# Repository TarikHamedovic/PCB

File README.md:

# Printed Circuit Board Projects

This github repo contains my PCB projects.

## Printed Circuit Board(PCB) Workshop

The workshop was held at the Faculty of Electrical Engineering in Sarajevo, participants were guided through the comprehensive process of manually crafting a Printed Circuit Board (PCB), from the initial design phase in software to the physical realization involving drilling and soldering. The centerpiece of this hands-on session was the construction of a simple yet effective audio amplifier circuit, centered around the versatile LM386 Integrated Circuit (IC). The design phase is done in Proteus because most students at the faculty are familiar with the software.

For educational purposes, we opted to design the PCB as a single-layer board with through-hole components. While it's feasible to construct a more compact version, we intentionally enlarged the board's dimensions. This decision was made to accommodate a safer and more participant-friendly drilling experience. Ensuring ease of handling and reducing the risk of errors during the manual drilling process were our primary considerations, making the workshop accessible and engaging for attendees, regardless of their prior experience with PCB fabrication.

Schematic of Audio Amplifier Circuit             |  PCB Layout of Audio Amplifier Circuit
:-------------------------:|:-------------------------:
  |  

## Ultrasonic Speaker

The PCB developed was a component of my Bachelor's Thesis, which focused on creating an ultrasonic directional speaker. To achieve this, I employed a digital modulation method utilizing an STM32 Nucleo microcontroller. Specifically, I designed a custom shield equipped with all necessary components to interface with the Nucleo board. Additionally, I designed an ultrasonic phased array to facilitate the directional output of ultrasonic waves. The PCB was made in Eagle software.

Schematic of STM32 Shield             |  PCB Layout of STM32 Shield
:-------------------------:|:-------------------------:
  |  

Schematic of Transducer Array             |  PCB Layout of Transducer Array
:-------------------------:|:-------------------------:
  |

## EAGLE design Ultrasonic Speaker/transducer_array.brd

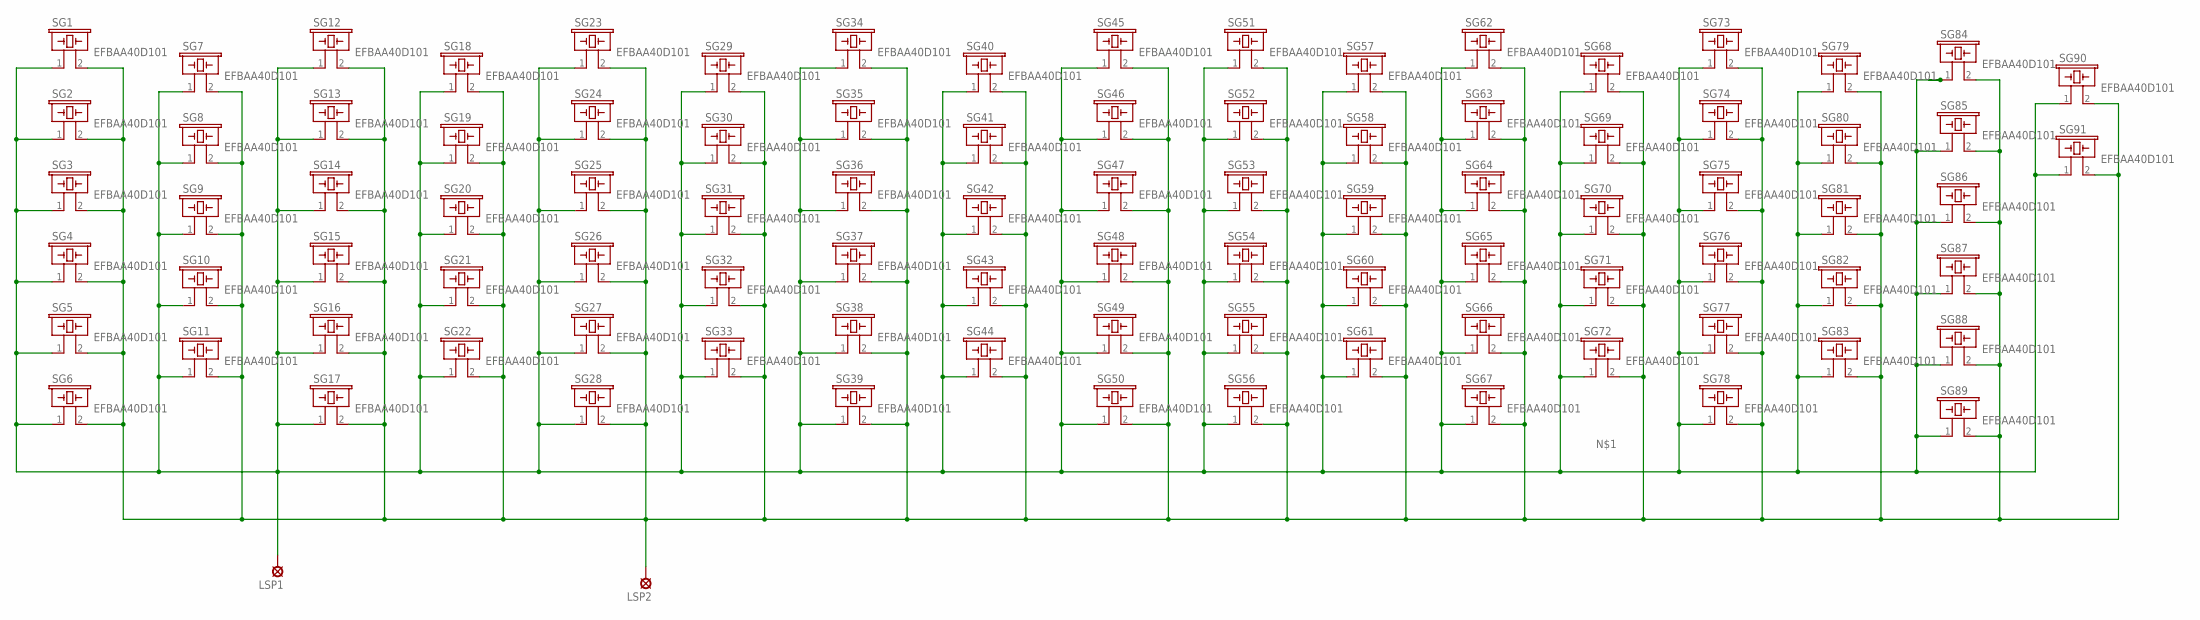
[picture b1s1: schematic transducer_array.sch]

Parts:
LSP1, LSP2: LSP10
SG1, SG2, SG3, SG4, SG5, SG6, SG7, SG8, SG9, SG10, SG11, SG12, SG13, SG14, SG15, SG16, SG17, SG18, SG19, SG20, SG21, SG22, SG23, SG24, SG25, SG26, SG27, SG28, SG29, SG30, SG31, SG32, SG33, SG34, SG35, SG36, SG37, SG38, SG39, SG40, SG41, SG42, SG43, SG44, SG45, SG46, SG47, SG48, SG49, SG50, SG51, SG52, SG53, SG54, SG55, SG56, SG57, SG58, SG59, SG60, SG61, SG62, SG63, SG64, SG65, SG66, SG67, SG68, SG69, SG70, SG71, SG72, SG73, SG74, SG75, SG76, SG77, SG78, SG79, SG80, SG81, SG82, SG83, SG84, SG85, SG86, SG87, SG88, SG89, SG90, SG91: EFBAA40D101

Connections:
unnamed: LSP1.MP, SG1.1, SG2.1, SG3.1, SG4.1, SG5.1, SG6.1, SG7.1, SG8.1, SG9.1, SG10.1, SG11.1, SG12.1, SG13.1, SG14.1, SG15.1, SG16.1, SG17.1, SG18.1, SG19.1, SG20.1, SG21.1, SG22.1, SG23.1, SG24.1, SG25.1, SG26.1, SG27.1, SG28.1, SG29.1, SG30.1, SG31.1, SG32.1, SG33.1, SG34.1, SG35.1, SG36.1, SG37.1, SG38.1, SG39.1, SG40.1, SG41.1, SG42.1, SG43.1, SG44.1, SG45.1, SG46.1, SG47.1, SG48.1, SG49.1, SG50.1, SG51.1, SG52.1, SG53.1, SG54.1, SG55.1, SG56.1, SG57.1, SG58.1, SG59.1, SG60.1, SG61.1, SG62.1, SG63.1, SG64.1, SG65.1, SG66.1, SG67.1, SG68.1, SG69.1, SG70.1, SG71.1, SG72.1, SG73.1, SG74.1, SG75.1, SG76.1, SG77.1, SG78.1, SG79.1, SG80.1, SG81.1, SG82.1, SG83.1, SG84.1, SG85.1, SG86.1, SG87.1, SG88.1, SG89.1, SG90.1, SG91.1
unnamed: LSP2.MP, SG1.2, SG2.2, SG3.2, SG4.2, SG5.2, SG6.2, SG7.2, SG8.2, SG9.2, SG10.2, SG11.2, SG12.2, SG13.2, SG14.2, SG15.2, SG16.2, SG17.2, SG18.2, SG19.2, SG20.2, SG21.2, SG22.2, SG23.2, SG24.2, SG25.2, SG26.2, SG27.2, SG28.2, SG29.2, SG30.2, SG31.2, SG32.2, SG33.2, SG34.2, SG35.2, SG36.2, SG37.2, SG38.2, SG39.2, SG40.2, SG41.2, SG42.2, SG43.2, SG44.2, SG45.2, SG46.2, SG47.2, SG48.2, SG49.2, SG50.2, SG51.2, SG52.2, SG53.2, SG54.2, SG55.2, SG56.2, SG57.2, SG58.2, SG59.2, SG60.2, SG61.2, SG62.2, SG63.2, SG64.2, SG65.2, SG66.2, SG67.2, SG68.2, SG69.2, SG70.2, SG71.2, SG72.2, SG73.2, SG74.2, SG75.2, SG76.2, SG77.2, SG78.2, SG79.2, SG80.2, SG81.2, SG82.2, SG83.2, SG84.2, SG85.2, SG86.2, SG87.2, SG88.2, SG89.2, SG90.2, SG91.2

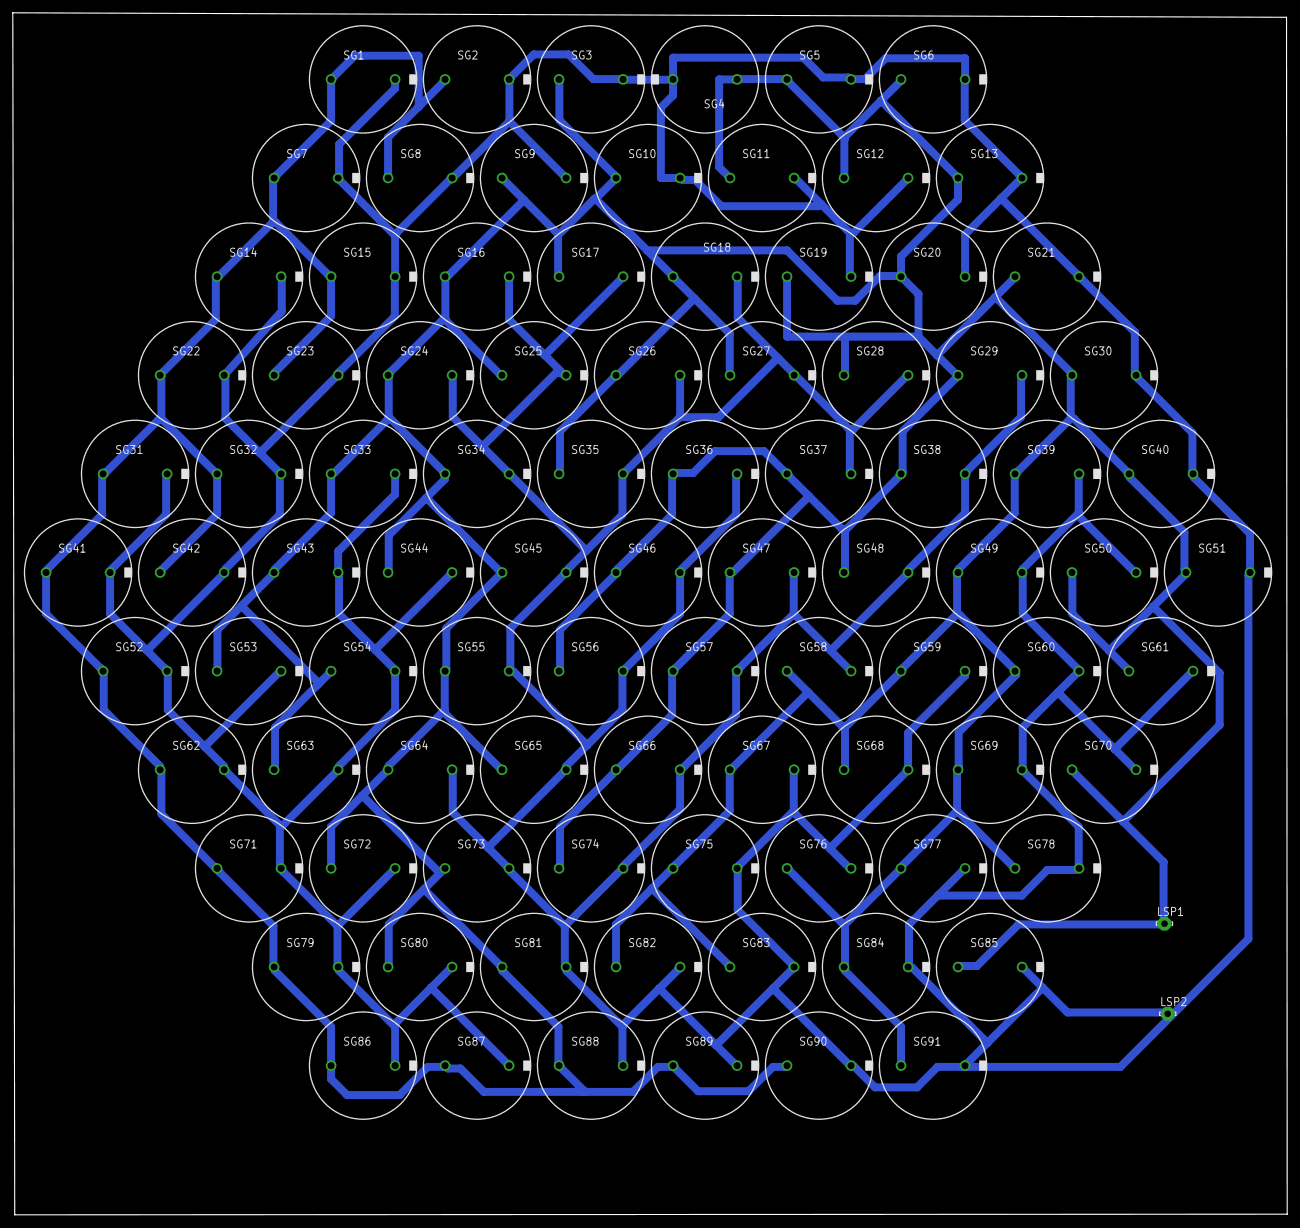
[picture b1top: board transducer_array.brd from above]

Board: 2 copper layers, 199.0 x 187.7 mm, 93 parts (0 on the bottom side), 2 nets.

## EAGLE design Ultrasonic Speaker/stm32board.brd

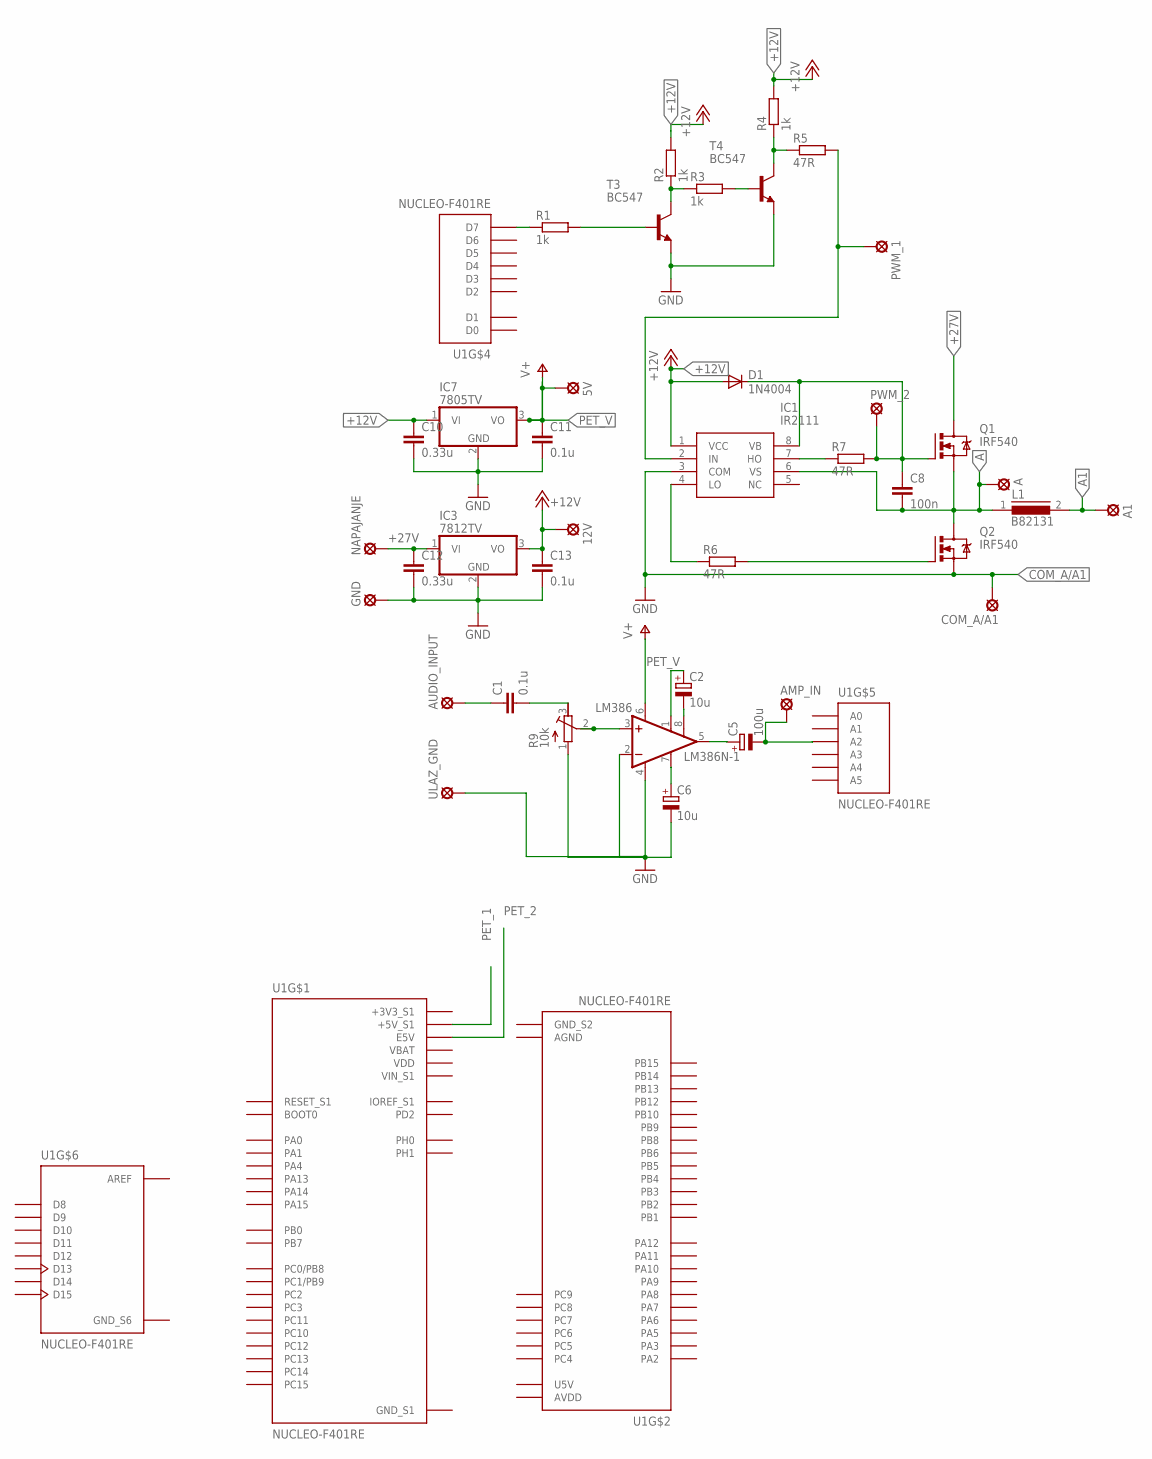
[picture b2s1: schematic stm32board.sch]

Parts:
5V, 12V: LSP10
A, A1: LSP10
AMP_IN: LSP10
AUDIO_INPUT: LSP10
C1, C11, C13: 0.1u; C050-030X075
C2, C6: 10u; E2,5-6E
C5: 100u; E2,5-6E
C8: 100n; C050-030X075
C10, C12: 0.33u; C050-030X075
COM_A/A1: LSP10
D1: 1N4004; DO41-10
GND: LSP10
IC1: IR2111; DIP762W56P254L988H533Q8N
IC3: 7812TV; TO220V
IC7: 7805TV; TO220V
L1: B82131; SUKW1-17
LM386: LM386N-1; DIL08
NAPAJANJE: LSP10
PWM_1, PWM_2: LSP10
Q1, Q2: IRF540; TO220BV
R1, R2, R3, R4: 1k; 0207/12
R5, R6, R7: 47R; 0207/12
R9: 10k; RTRIM3339P
T3, T4: BC547; TO92
U1: NUCLEO-F401RE; ST_NUCLEO-F401RE
ULAZ_GND: LSP10

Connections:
+3V3: U1.CN6_4 (+3V3)
+3V3_S1: U1.CN7_16 (+3V3_S1)
+12V: 12V.MP, C10.1, C13.1, D1.A, IC1.1 (VCC), IC3.3 (VO), IC7.1 (VI), R2.2, R4.2
+27V: C12.1, IC3.1 (VI), NAPAJANJE.MP, Q1.D
A: A.MP, C8.2, IC1.6 (VS), L1.1, Q1.S, Q2.D
A1: A1.MP, L1.2
AGND: U1.CN10_32 (AGND)
AREF: U1.CN5_8 (AREF)
AUDIO_INPUT: AUDIO_INPUT.MP, C1.1
AVDD: U1.CN10_7 (AVDD)
COM_A/A1: COM_A/A1.MP, IC1.3 (COM), Q2.S
GND: C6.-, C10.2, C11.2, C12.2, C13.2, GND.MP, IC3.2 (GND), IC7.2 (GND), LM386.2 (-IN), LM386.4 (GND), R9.1 (A), T3.1 (E), T4.1 (E), U1.CN6_6 (GND), U1.CN6_7 (GND), ULAZ_GND.MP
GND_S1: U1.CN7_8 (GND_S1), U1.CN7_19 (GND_S1), U1.CN7_20 (GND_S1), U1.CN7_22 (GND_S1)
GND_S2: U1.CN10_9 (GND_S2), U1.CN10_20 (GND_S2)
GND_S6: U1.CN5_7 (GND_S6)
unnamed: C5.+, LM386.5 (OUT)
unnamed: AMP_IN.MP, C5.-, U1.CN8_3 (A2)
unnamed: C2.-, LM386.8 (GAIN)
unnamed: C6.+, LM386.7 (BYPASS)
unnamed: R1.1, U1.CN9_8 (D7)
unnamed: C1.2, R9.3 (E)
unnamed: C2.+, LM386.1 (GAIN)
unnamed: LM386.3 (+IN), R9.2 (S)
unnamed: R1.2, T3.2 (B)
unnamed: R2.1, R3.1, T3.3 (C)
unnamed: R4.1, R5.1, T4.3 (C)
unnamed: R3.2, T4.2 (B)
unnamed: IC1.7 (HO), R7.1
unnamed: C8.1, D1.C, IC1.8 (VB), PWM_2.MP, Q1.G, R7.2
unnamed: IC1.4 (LO), R6.1
unnamed: Q2.G, R6.2
unnamed: IC1.2 (IN), PWM_1.MP, R5.2
PET_1: U1.CN7_18 (+5V_S1)
PET_2: U1.CN7_6 (E5V)
PET_V: 5V.MP, C11.1, IC7.3 (VO), LM386.6 (VS), U1.CN6_5 (+5V)
U5V: U1.CN10_8 (U5V)
VBAT: U1.CN7_33 (VBAT)
VDD: U1.CN7_5 (VDD)
VIN: U1.CN6_8 (VIN)
VIN_S1: U1.CN7_24 (VIN_S1)

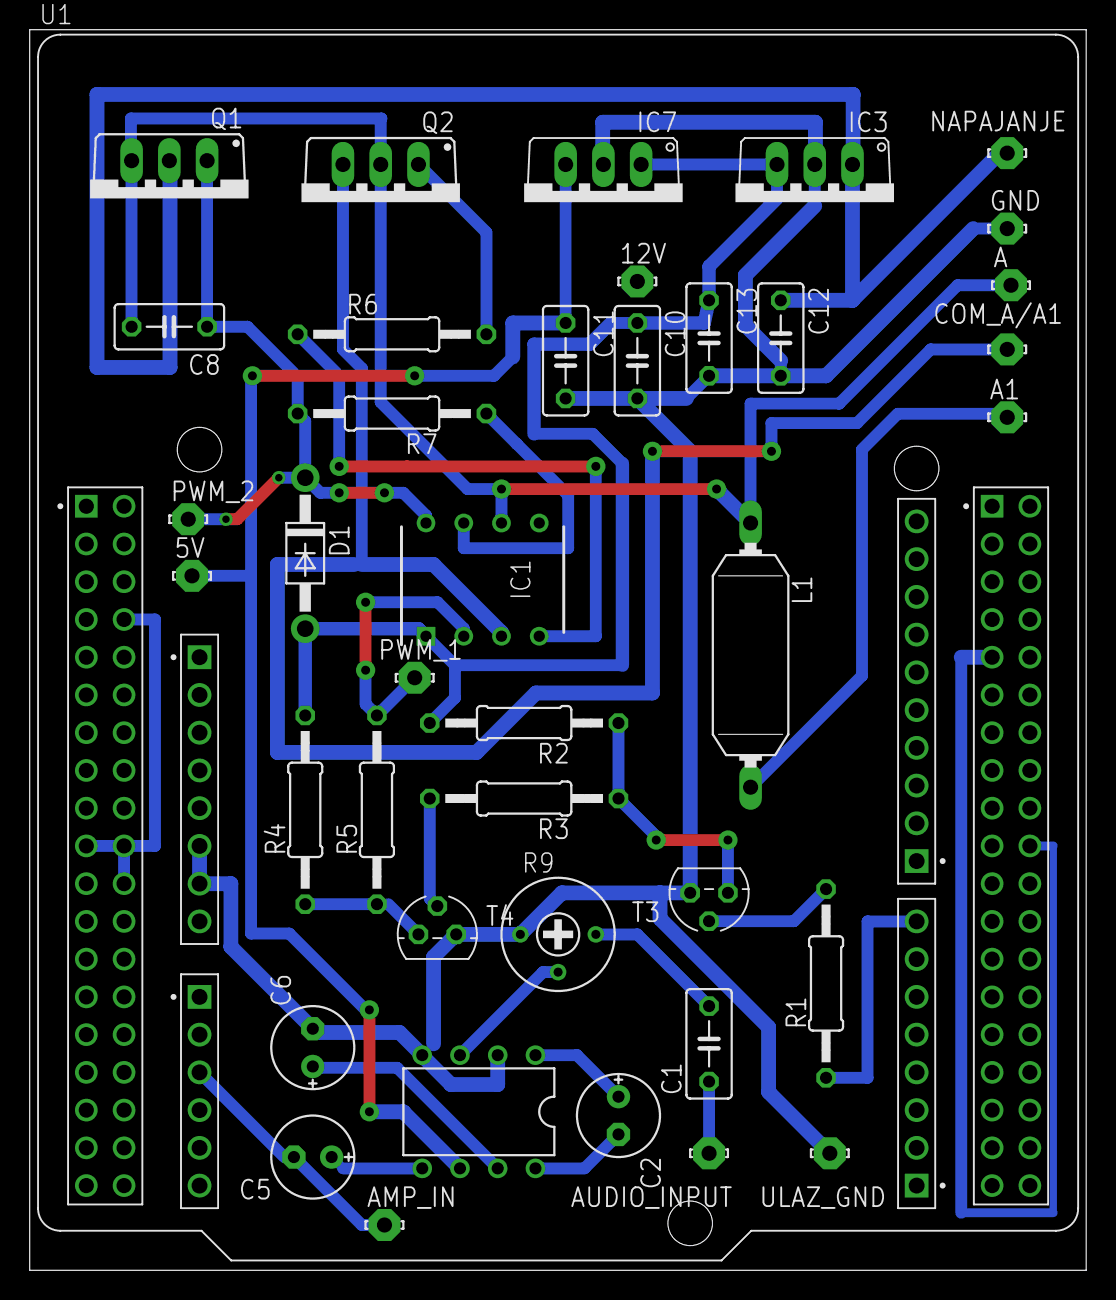
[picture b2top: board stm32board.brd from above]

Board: 2 copper layers, 71.1 x 83.5 mm, 40 parts (0 on the bottom side), 27 nets.
